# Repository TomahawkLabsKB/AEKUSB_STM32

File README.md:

# AEKUSB_STM32
Drop in PCB for the Apple M3501 using a STM32 daughter board.

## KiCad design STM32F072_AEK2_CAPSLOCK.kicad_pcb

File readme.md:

# aek2stm32

*A short description of the keyboard/project*

* Keyboard Maintainer: [Steven Tomanek](https://github.com/tomahawklabskb)
* Hardware Supported: *The PCBs, controllers supported*
* Hardware Availability: *Links to where you can find this hardware*

Make example for this keyboard (after setting up your build environment):

    make aek2stm32:default

Flashing example for this keyboard:

    make aek2stm32:default:flash

See the [build environment setup](https://docs.qmk.fm/#/getting_started_build_tools) and the [make instructions](https://docs.qmk.fm/#/getting_started_make_guide) for more information. Brand new to QMK? Start with our [Complete Newbs Guide](https://docs.qmk.fm/#/newbs).

## Bootloader

Enter the bootloader in 3 ways:

* **Bootmagic reset**: Hold down the key at (0,0) in the matrix (usually the top left key or Escape) and plug in the keyboard
* **Physical reset button**: Briefly press the button on the back of the PCB - some may have pads you must short instead
* **Keycode in layout**: Press the key mapped to `QK_BOOT` if it is available

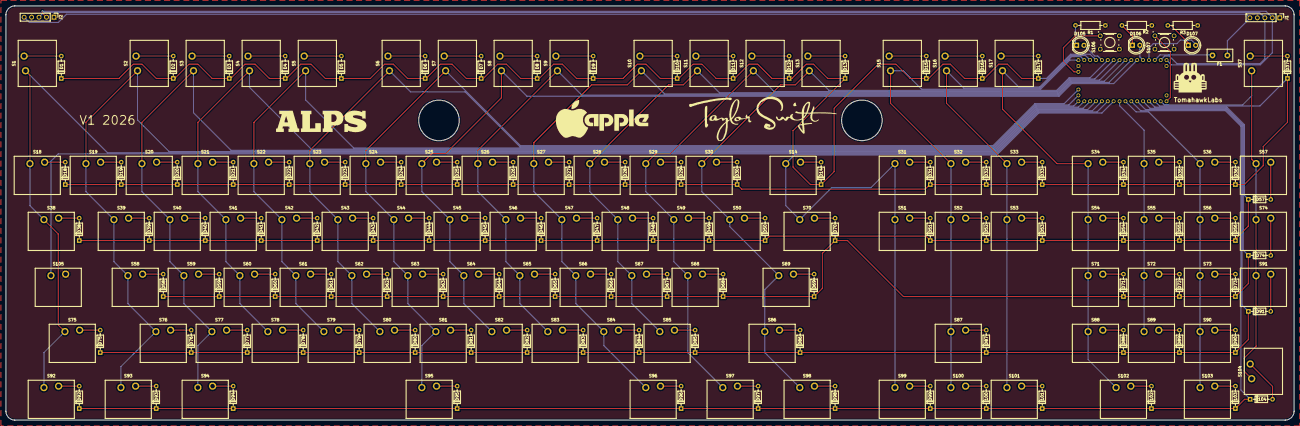
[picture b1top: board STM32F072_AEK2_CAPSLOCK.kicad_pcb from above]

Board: 2 copper layers, 438.3 x 140.9 mm, 221 parts (0 on the bottom side), 144 nets.

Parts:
100, 101, 102, 103, 104: Diode; THT Diode
D1, D2, D3, D4, D5, D6, D7, D8, D9, D10, D11, D12, D13, D14, D15, D16, D17, D18, D19, D20, D21, D22, D23, D24, D25, D26, D27, D28, D29, D30, D31, D32, D33, D34, D35, D36, D37, D38, D39, D40, D41, D42, D43, D44, D45, D46, D47, D48, D49, D50, D51, D52, D53, D54, D55, D56, D57, D58, D59, D60, D61, D62, D63, D64, D65, D66, D67, D68, D69, D70, D71, D72, D73, D74, D75, D76, D77, D78, D79, D80, D81, D82, D83, D84, D85, D86, D87, D88, D89, D90, D91, D92, D93, D94, D95, D96, D97, D98, D99: Diode; THT Diode
D105, D106, D107: LED; LED_D5.0mm
F1: 500mA; Fuse_Littelfuse_395Series
J1, J2: Conn_01x05_Pin; PinHeader_1x05_P2.54mm_Vertical
R1, R2, R3: 220R; R_Axial_DIN0207_L6.3mm_D2.5mm_P10.16mm_Horizontal
S1: Escape; Alps_1.00u
S2: F1; Alps_1.00u
S3: F2; Alps_1.00u
S4: F3; Alps_1.00u
S5: F4; Alps_1.00u
S6: F5; Alps_1.00u
S7: F6; Alps_1.00u
S8: F7; Alps_1.00u
S9: F8; Alps_1.00u
S10: F9; Alps_1.00u
S11: F10; Alps_1.00u
S12: F11; Alps_1.00u
S13: F12; Alps_1.00u
S14: Backspace; Alps_2.00u
S15: F13; Alps_1.00u
S16: F14; Alps_1.00u
S17: F15; Alps_1.00u
S18: `~; Alps_1.00u
S19: 1; Alps_1.00u
S20: 2; Alps_1.00u
S21: 3; Alps_1.00u
S22: 4; Alps_1.00u
S23: 5; Alps_1.00u
S24: 6; Alps_1.00u
S25: 7; Alps_1.00u
S26: 8; Alps_1.00u
S27: 9; Alps_1.00u
S28: 0; Alps_1.00u
S29: -_; Alps_1.00u
S30: =+; Alps_2.00u
S31: INSERT; Alps_1.00u
S32: HOME; Alps_1.00u
S33: PGUP; Alps_1.00u
S34: NUMLOCK; Alps_1.00u
S35: NUM_=; Alps_1.00u
S36: NUM_/; Alps_1.00u
S37: Eject; Alps_1.00u
S38: TAB; Alps_1.50u
S39: Q; Alps_1.00u
S40: W; Alps_1.00u
S41: E; Alps_1.00u
S42: R; Alps_1.00u
S43: T; Alps_1.00u
S44: Y; Alps_1.00u
S45: U; Alps_1.00u
S46: I; Alps_1.00u
S47: O; Alps_1.00u
S48: P; Alps_1.00u
S49: [; Alps_1.00u
S50: ]; Alps_1.00u
S51: DEL; Alps_1.00u
S52: END; Alps_1.00u
S53: PGDN; Alps_1.00u
S54: NUM_7; Alps_1.00u
S55: NUM_8; Alps_1.00u
S56: NUM_9; Alps_1.00u
S57: NUM_*; Alps_1.00u
S58: A; Alps_1.00u
S59: S; Alps_1.00u
S60: D; Alps_1.00u
S61: F; Alps_1.00u
S62: G; Alps_1.00u
S63: H; Alps_1.00u
S64: J; Alps_1.00u
S65: K; Alps_1.00u
S66: L; Alps_1.00u
S67: ;:; Alps_1.00u
S68: "'; Alps_1.00u
S69: ENTER; Alps_1.00u
S70: \; Alps_2.25u
S71: NUM_4; Alps_1.50u
S72: NUM_5; Alps_1.00u
S73: NUM_6; Alps_1.00u
S74: NUM_-; Alps_1.00u
S75: L_SHIFT; Alps_1.00u
S76: Z; Alps_2.25u
S77: X; Alps_1.00u
S78: C; Alps_1.00u
S79: V; Alps_1.00u
S80: B; Alps_1.00u
S81: N; Alps_1.00u
S82: M; Alps_1.00u
S83: <,; Alps_1.00u
S84: >.; Alps_1.00u
S85: ?/; Alps_1.00u
S86: R_SHIFT; Alps_1.00u
S87: UP; Alps_2.75u
S88: NUM_1; Alps_1.00u
S89: NUM_2; Alps_1.00u
S90: NUM_3; Alps_1.00u
S91: NUM_+; Alps_1.00u
S92: L_CONTROL; Alps_1.50u
S93: L_ALT; Alps_1.25u
S94: L_META; Alps_1.50u
S95: SPACE; Alps_6.50u
S96: R_META; Alps_1.50u
S97: R_ALT; Alps_1.25u
S98: R_CONTROL; Alps_1.50u
S99: LEFT; Alps_1.00u
S100: DOWN; Alps_1.00u
S101: RIGHT; Alps_1.00u
S102: NUM_0; Alps_2.00u
S103: NUM_.; Alps_1.00u
S104: NUM_ENTER; Alps_2.00u
S105: CAPSLOCK; Alps_1.75u
S106: Reset; SW_B3F-1000
S107: Bootsel; SW_B3F-1000
U3: kb_f072

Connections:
Bootsel: S107.1, U3.32 (BOOT0)
CapsLock_LED: D106.2 (A), U3.5 (B3)
Capslock_Switch: S105.1, U3.22 (B1)
Column00: S1.1, S18.1, S38.1, S75.1, S92.1, U3.21 (B0)
Column01: S2.1, S19.1, S39.1, S58.1, S76.1, S93.1, U3.20 (A7)
Column02: S3.1, S20.1, S40.1, S59.1, S77.1, S94.1, U3.19 (A6)
Column03: S4.1, S21.1, S41.1, S60.1, S78.1, U3.18 (A5)
Column04: S5.1, S22.1, S42.1, S61.1, S79.1, U3.17 (A4)
Column05: S6.1, S23.1, S43.1, S62.1, S80.1, U3.36 (A3)
Column06: S7.1, S24.1, S44.1, S63.1, S81.1, S95.1, U3.35 (A2)
Column07: S8.1, S25.1, S45.1, S64.1, S82.1, U3.6 (B4)
Column08: S9.1, S26.1, S46.1, S65.1, S83.1, U3.7 (B5)
Column09: S10.1, S27.1, S47.1, S66.1, S84.1, S96.1, U3.8 (B8)
Column10: S11.1, S28.1, S48.1, S67.1, S85.1, U3.9 (B9)
Column11: S12.1, S29.1, S49.1, S68.1, S97.1, U3.10 (C13)
Column12: S13.1, S30.1, S50.1, S69.1, S86.1, S98.1, U3.11 (C14)
Column13: S14.1, S31.1, S51.1, S70.1, S99.1, U3.23 (B2)
Column14: S15.1, S32.1, S52.1, S87.1, S100.1, U3.16 (A0)
Column15: S16.1, S33.1, S53.1, S101.1, U3.15 (A1)
Column16: S17.1, S34.1, S54.1, S71.1, S88.1, S102.1, U3.14 (F1)
Column17: S35.1, S55.1, S72.1, S89.1, U3.24 (B10)
Column18: S36.1, S56.1, S73.1, S90.1, S103.1, U3.25 (B12)
Column19: S37.1, S57.1, S74.1, S91.1, S104.1, U3.31 (A10)
GND: J1.1, J1.4, J2.1, J2.4, R1.1, R2.1, R3.1, S105.2, S106.3, S106.4, S107.3, S107.4, U3.33 (GND), U3.38 (GND)
unnamed: D1.2 (A), S1.2
unnamed: D2.2 (A), S2.2
unnamed: D3.2 (A), S3.2
unnamed: D4.2 (A), S4.2
unnamed: D5.2 (A), S5.2
unnamed: D6.2 (A), S6.2
unnamed: D7.2 (A), S7.2
unnamed: D8.2 (A), S8.2
unnamed: D9.2 (A), S9.2
unnamed: D10.2 (A), S10.2
unnamed: D11.2 (A), S11.2
unnamed: D12.2 (A), S12.2
unnamed: D13.2 (A), S13.2
unnamed: D14.2 (A), S14.2
unnamed: D15.2 (A), S15.2
unnamed: D16.2 (A), S16.2
unnamed: D17.2 (A), S17.2
unnamed: D18.2 (A), S18.2
unnamed: D19.2 (A), S19.2
unnamed: D20.2 (A), S20.2
unnamed: D21.2 (A), S21.2
unnamed: D22.2 (A), S22.2
unnamed: D23.2 (A), S23.2
unnamed: D24.2 (A), S24.2
unnamed: D25.2 (A), S25.2
unnamed: D26.2 (A), S26.2
unnamed: D27.2 (A), S27.2
unnamed: D28.2 (A), S28.2
unnamed: D29.2 (A), S29.2
unnamed: D30.2 (A), S30.2
unnamed: D31.2 (A), S31.2
unnamed: D32.2 (A), S32.2
unnamed: D33.2 (A), S33.2
unnamed: D34.2 (A), S34.2
unnamed: D35.2 (A), S35.2
unnamed: D36.2 (A), S36.2
unnamed: D37.2 (A), S37.2
unnamed: D38.2 (A), S38.2
unnamed: D39.2 (A), S39.2
unnamed: D40.2 (A), S40.2
unnamed: D41.2 (A), S41.2
unnamed: D42.2 (A), S42.2
unnamed: D43.2 (A), S43.2
unnamed: D44.2 (A), S44.2
unnamed: D45.2 (A), S45.2
unnamed: D46.2 (A), S46.2
unnamed: D47.2 (A), S47.2
unnamed: D48.2 (A), S48.2
unnamed: D49.2 (A), S49.2
unnamed: D50.2 (A), S50.2
unnamed: D51.2 (A), S51.2
unnamed: D52.2 (A), S52.2
unnamed: D53.2 (A), S53.2
unnamed: D54.2 (A), S54.2
unnamed: D55.2 (A), S55.2
unnamed: D56.2 (A), S56.2
unnamed: D57.2 (A), S57.2
unnamed: D58.2 (A), S58.2
unnamed: D59.2 (A), S59.2
unnamed: D60.2 (A), S60.2
unnamed: D61.2 (A), S61.2
unnamed: D62.2 (A), S62.2
unnamed: D63.2 (A), S63.2
unnamed: D64.2 (A), S64.2
unnamed: D65.2 (A), S65.2
unnamed: D66.2 (A), S66.2
unnamed: D67.2 (A), S67.2
unnamed: D68.2 (A), S68.2
unnamed: D69.2 (A), S69.2
unnamed: D70.2 (A), S70.2
unnamed: D71.2 (A), S71.2
unnamed: D72.2 (A), S72.2
unnamed: D73.2 (A), S73.2
unnamed: D74.2 (A), S74.2
unnamed: D75.2 (A), S75.2
unnamed: D76.2 (A), S76.2
unnamed: D77.2 (A), S77.2
unnamed: D78.2 (A), S78.2
unnamed: D79.2 (A), S79.2
unnamed: D80.2 (A), S80.2
unnamed: D81.2 (A), S81.2
unnamed: D82.2 (A), S82.2
unnamed: D83.2 (A), S83.2
unnamed: D84.2 (A), S84.2
unnamed: D85.2 (A), S85.2
unnamed: D86.2 (A), S86.2
unnamed: D87.2 (A), S87.2
unnamed: D88.2 (A), S88.2
unnamed: D89.2 (A), S89.2
unnamed: D90.2 (A), S90.2
unnamed: D91.2 (A), S91.2
unnamed: D92.2 (A), S92.2
unnamed: D93.2 (A), S93.2
unnamed: D94.2 (A), S94.2
unnamed: D95.2 (A), S95.2
unnamed: D96.2 (A), S96.2
unnamed: D97.2 (A), S97.2
unnamed: D98.2 (A), S98.2
unnamed: D99.2 (A), S99.2
unnamed: 100.2 (A), S100.2
unnamed: 101.2 (A), S101.2
unnamed: 102.2 (A), S102.2
unnamed: 103.2 (A), S103.2
unnamed: 104.2 (A), S104.2
unnamed: D105.1 (K), R1.2
unnamed: D106.1 (K), R2.2
unnamed: D107.1 (K), R3.2
NumLock_LED: D105.2 (A), U3.12 (C15)
Row00: D1.1 (K), D2.1 (K), D3.1 (K), D4.1 (K), D5.1 (K), D6.1 (K), D7.1 (K), D8.1 (K), D9.1 (K), D10.1 (K), D11.1 (K), D12.1 (K), D13.1 (K), D14.1 (K), D15.1 (K), D16.1 (K), D17.1 (K), U3.13 (F0)
Row01: D18.1 (K), D19.1 (K), D20.1 (K), D21.1 (K), D22.1 (K), D23.1 (K), D24.1 (K), D25.1 (K), D26.1 (K), D27.1 (K), D28.1 (K), D29.1 (K), D30.1 (K), D31.1 (K), D32.1 (K), D33.1 (K), D34.1 (K), D35.1 (K), D36.1 (K), D37.1 (K), U3.30 (A9)
Row02: D38.1 (K), D39.1 (K), D40.1 (K), D41.1 (K), D42.1 (K), D43.1 (K), D44.1 (K), D45.1 (K), D46.1 (K), D47.1 (K), D48.1 (K), D49.1 (K), D50.1 (K), D51.1 (K), D52.1 (K), D53.1 (K), D54.1 (K), D55.1 (K), D56.1 (K), D57.1 (K), U3.29 (A8)
Row03: D58.1 (K), D59.1 (K), D60.1 (K), D61.1 (K), D62.1 (K), D63.1 (K), D64.1 (K), D65.1 (K), D66.1 (K), D67.1 (K), D68.1 (K), D69.1 (K), D70.1 (K), D71.1 (K), D72.1 (K), D73.1 (K), D74.1 (K), U3.28 (B15)
Row04: D75.1 (K), D76.1 (K), D77.1 (K), D78.1 (K), D79.1 (K), D80.1 (K), D81.1 (K), D82.1 (K), D83.1 (K), D84.1 (K), D85.1 (K), D86.1 (K), D87.1 (K), D88.1 (K), D89.1 (K), D90.1 (K), D91.1 (K), U3.27 (B14)
Row05: 100.1 (K), 101.1 (K), 102.1 (K), 103.1 (K), 104.1 (K), D92.1 (K), D93.1 (K), D94.1 (K), D95.1 (K), D96.1 (K), D97.1 (K), D98.1 (K), D99.1 (K), U3.26 (B13)
Run: S106.1, U3.34 (RST)
ScrollLock_LED: D107.2 (A), U3.4 (PA15)
USB_DM: J1.3, J2.3, U3.2 (D-)
USB_DP: J1.2, J2.2, U3.1 (D+)
VBUS: F1.2, U3.3 (5V)
VBUS_USB: F1.1, J1.5, J2.5
